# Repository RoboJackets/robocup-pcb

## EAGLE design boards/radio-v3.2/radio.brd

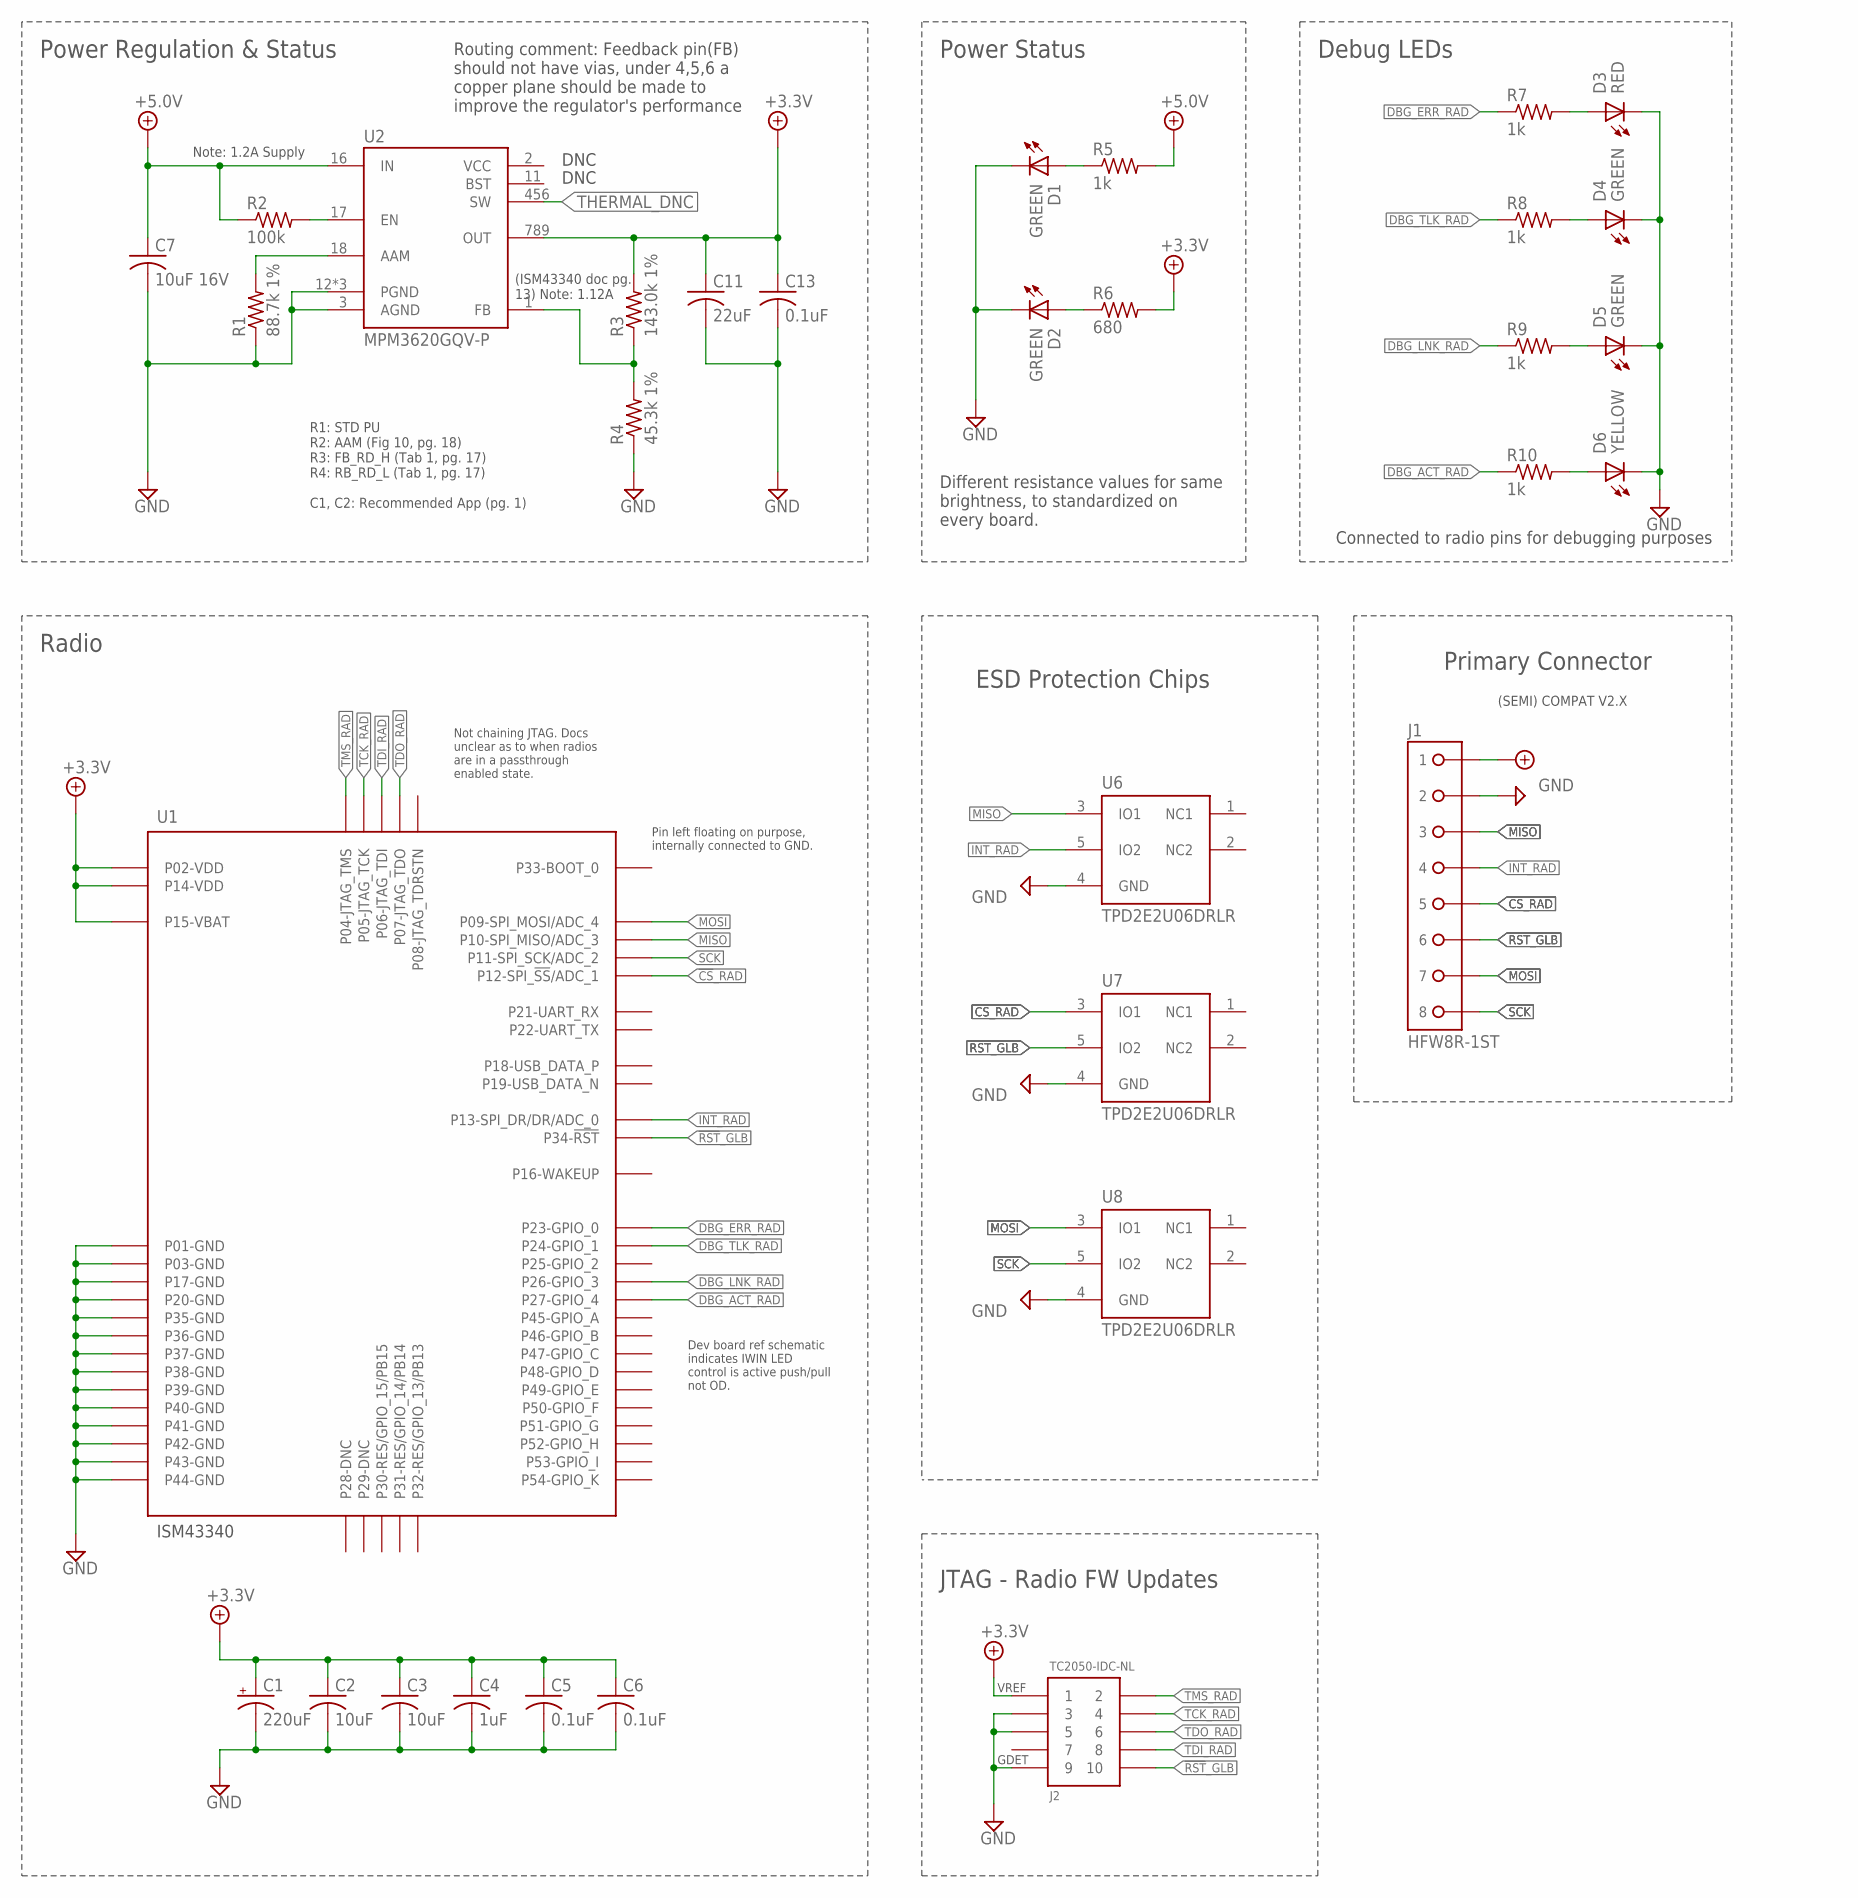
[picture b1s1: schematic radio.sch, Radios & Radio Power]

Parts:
C1: 220uF; ECA-0JM221-HGT_HORIZ
C2, C3: 10uF; C0805
C4: 1uF; C0603
C5, C6, C13: 0.1uF; C0603
C7: 10uF 16V; C1210
C11: 22uF; C1210
D1, D2, D4, D5: GREEN; CHIP-LED0603
D3: RED; CHIP-LED0603
D6: YELLOW; CHIP-LED0603
J1: HFW8R-1ST
J2: TC2050-IDC-NL
R1: 88.7k 1%; R0603
R2: 100k; R0603
R3: 143.0k 1%; R0603
R4: 45.3k 1%; R0603
R5, R7, R8, R9, R10: 1k; R0603
R6: 680; R0603
U1: ISM43340
U2: MPM3620GQV-P
U6, U7, U8: TPD2E2U06DRLR; SOT-553

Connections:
3V3_PWR_IND: D2.A, R6.1
5V_PWR_IND: D1.A, R5.1
!CS!_RAD: J1.5, U1.P$12 (P12-SPI_!SS!/ADC_1), U7.3 (IO1)
!RST!_GLB: J1.6, J2.10, U1.P$34 (P34-!RST!), U7.5 (IO2)
+3.3V: C1.P$1 (+), C2.1, C3.1, C4.1, C5.1, C6.1, C11.1, C13.1, J2.1, R3.2, R6.2, U1.P$2 (P02-VDD), U1.P$14 (P14-VDD), U1.P$15 (P15-VBAT), U2.789 (OUT)
+5.0V: C7.1, J1.1, R2.1, R5.2, U2.16 (IN)
AAM: R1.2, U2.18 (AAM)
DBG_ACT_RAD: R10.1, U1.P$27 (P27-GPIO_4)
DBG_ERR: D3.A, R7.2
DBG_ERR_RAD: R7.1, U1.P$23 (P23-GPIO_0)
DBG_LNK_RAD: R9.1, U1.P$26 (P26-GPIO_3)
DBG_TLK_RAD: R8.1, U1.P$24 (P24-GPIO_1)
DGB_ACT: D6.A, R10.2
DGB_LNK: D5.A, R9.2
EN: R2.2, U2.17 (EN)
FB: R3.1, R4.2, U2.1 (FB)
GND: C1.P$2 (-), C2.2, C3.2, C4.2, C5.2, C6.2, C7.2, C11.2, C13.2, D1.C (K), D2.C (K), D3.C (K), D4.C (K), D5.C (K), D6.C (K), J1.2, J2.3, J2.5, J2.9, R1.1, R4.1, U1.P$1 (P01-GND), U1.P$3 (P03-GND), U1.P$17 (P17-GND), U1.P$20 (P20-GND), U1.P$35 (P35-GND), U1.P$36 (P36-GND), U1.P$37 (P37-GND), U1.P$38 (P38-GND), U1.P$39 (P39-GND), U1.P$40 (P40-GND), U1.P$41 (P41-GND), U1.P$42 (P42-GND), U1.P$43 (P43-GND), U1.P$44 (P44-GND), U2.3 (AGND), U2.12 (PGND), U2.13 (PGND), U2.14 (PGND), U6.4 (GND), U7.4 (GND), U8.4 (GND)
INT_RAD: J1.4, U1.P$13 (P13-SPI_DR/DR/ADC_0), U6.5 (IO2)
MISO: J1.3, U1.P$10 (P10-SPI_MISO/ADC_3), U6.3 (IO1)
MOSI: J1.7, U1.P$9 (P09-SPI_MOSI/ADC_4), U8.3 (IO1)
SCK: J1.8, U1.P$11 (P11-SPI_SCK/ADC_2), U8.5 (IO2)
TCK_RAD: J2.4, U1.P$5 (P05-JTAG_TCK)
TDI_RAD: J2.8, U1.P$6 (P06-JTAG_TDI)
TDO_RAD: J2.6, U1.P$7 (P07-JTAG_TDO)
THERMAL_DNC: U2.456 (SW)
TLK: D4.A, R8.2
TMS_RAD: J2.2, U1.P$4 (P04-JTAG_TMS)

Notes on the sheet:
DNC
Primary Connector
Power Regulation & Status
Power Status
Note: 1.2A Supply
(ISM43340 doc pg. 13) Note: 1.12A
R1: STD PU R2: AAM (Fig 10, pg. 18) R3: FB_RD_H (Tab 1, pg. 17) R4: RB_RD_L (Tab 1, pg. 17) C1, C2: Recommended App (pg. 1)
Radio
Debug LEDs
VREF
GDET
JTAG - Radio FW Updates
Dev board ref schematic indicates IWIN LED control is active push/pull not OD.
Not chaining JTAG. Docs unclear as to when radios are in a passthrough enabled state.
(SEMI) COMPAT V2.X
ESD Protection Chips
Pin left floating on purpose, internally connected to GND.
Routing comment: Feedback pin(FB) should not have vias, under 4,5,6 a copper plane should be made to improve the regulator's performance
Connected to radio pins for debugging purposes
Different resistance values for same brightness, to standardized on every board.

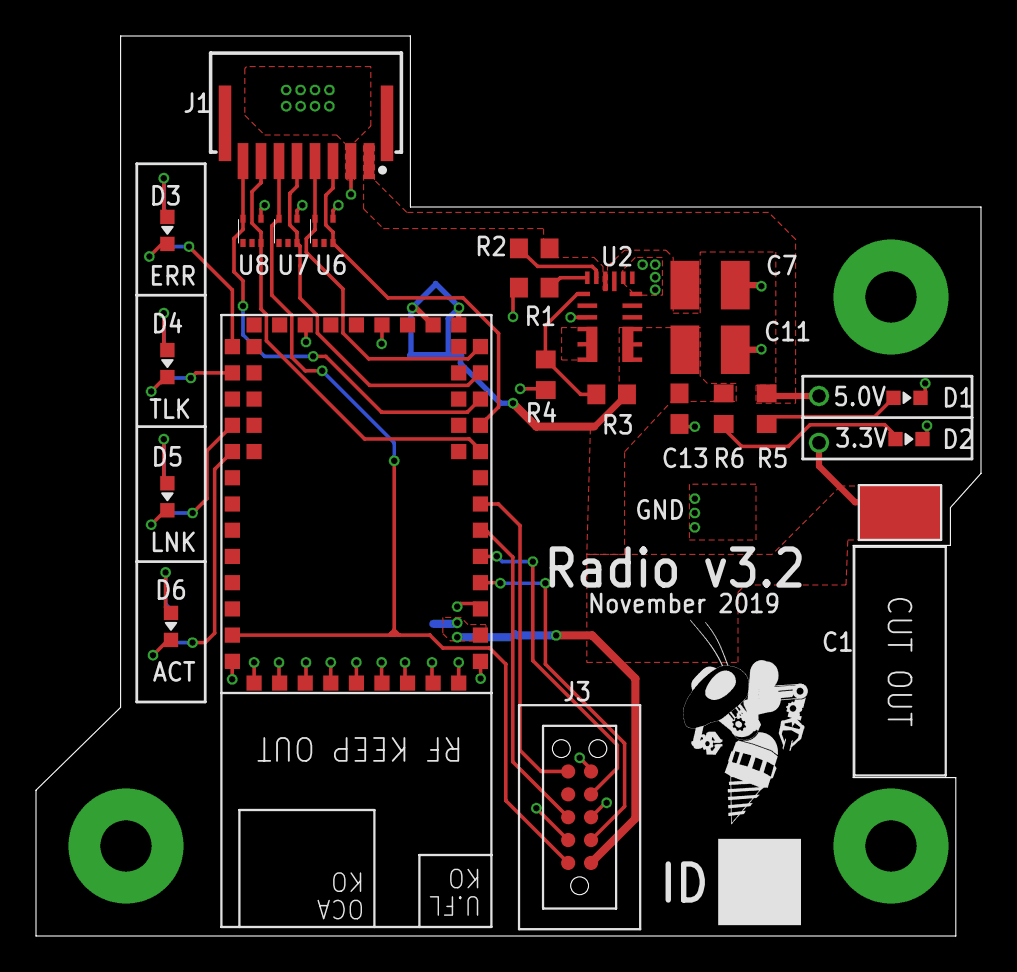
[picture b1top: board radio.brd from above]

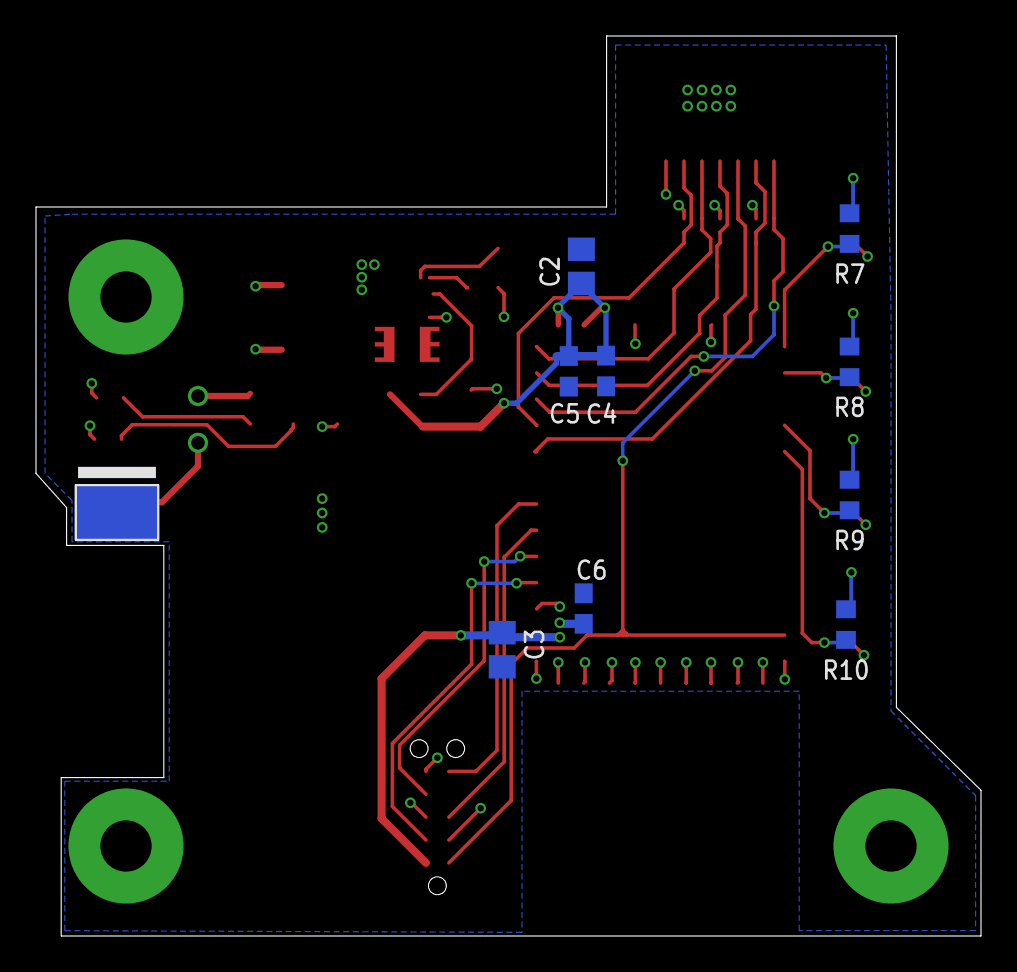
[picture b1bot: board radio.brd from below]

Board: 2 copper layers, 52.5 x 50.0 mm, 33 parts (9 on the bottom side), 26 nets.

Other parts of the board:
U$1: ROBOBUZZ_0.6X

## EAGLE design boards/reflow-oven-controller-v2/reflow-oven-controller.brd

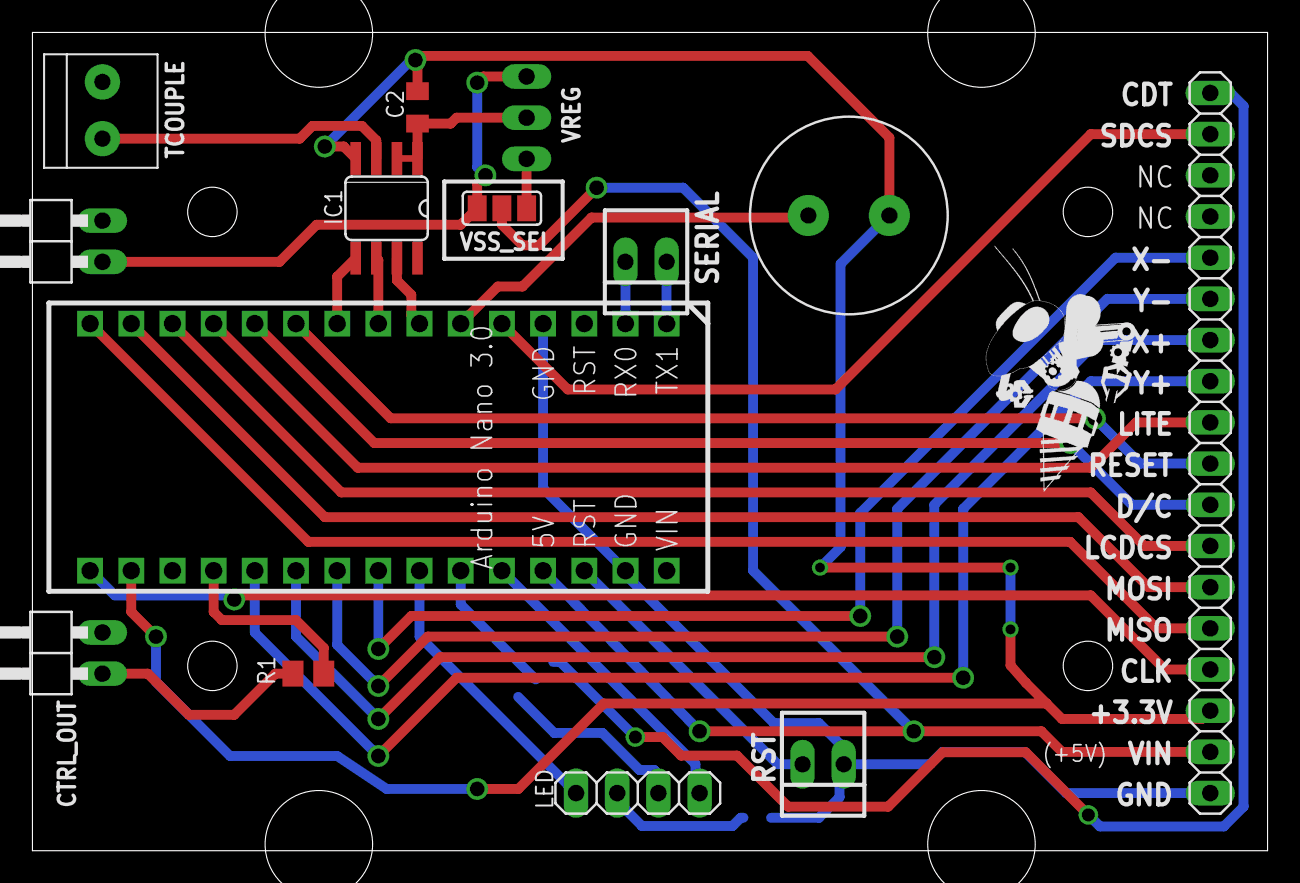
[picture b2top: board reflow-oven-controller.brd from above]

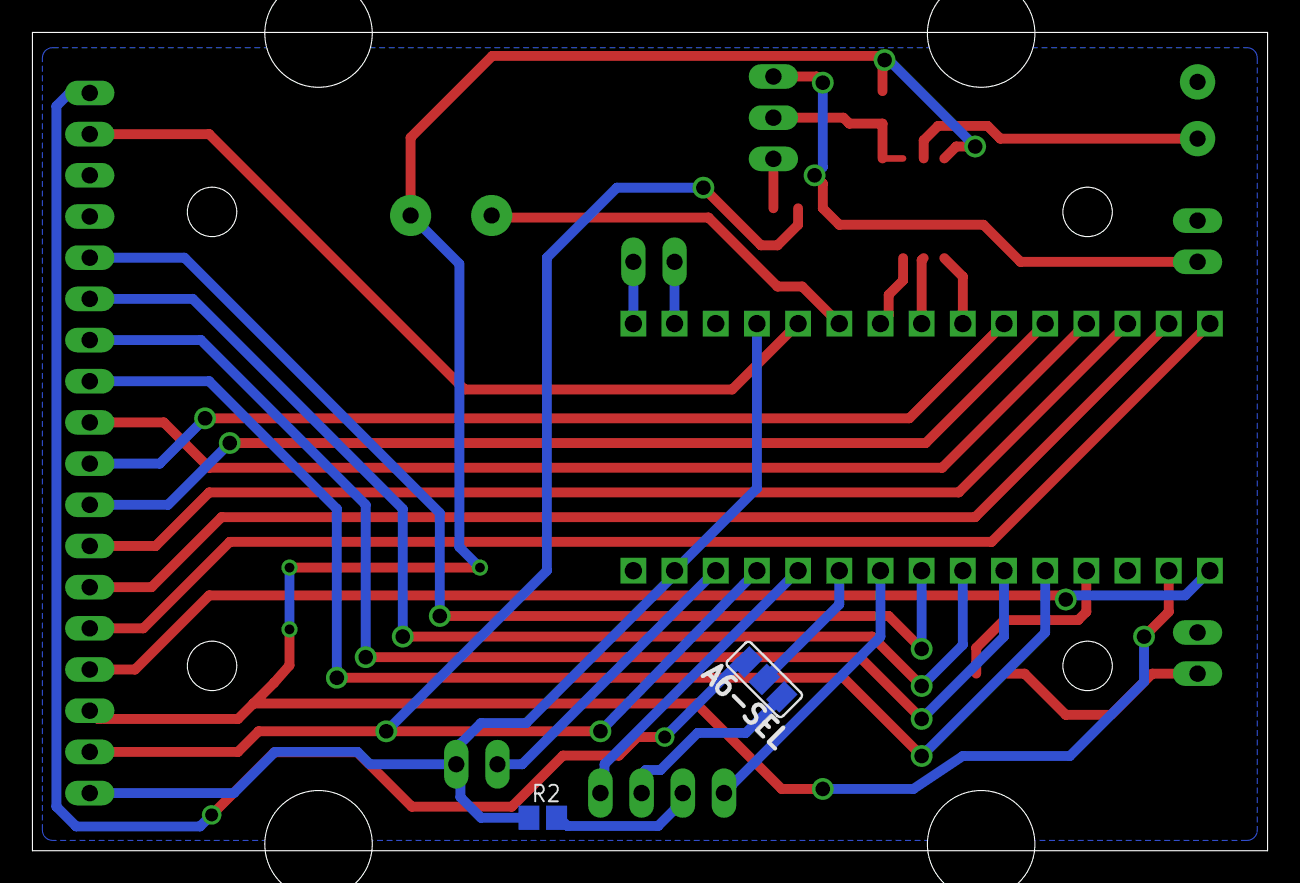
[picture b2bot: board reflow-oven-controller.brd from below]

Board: 2 copper layers, 76.2 x 50.5 mm, 17 parts (2 on the bottom side), 33 nets.

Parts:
A6-SEL: SJ_2
C2: 0.1uF; C0805K
IC1: MAX6675; SO08
JP1: CTRL_OUT; 1X02/90
JP2: VIN; 1X02/90
JP4: 1X18
LED: RGB Led Common Anode; 1X04
R1: 60; M0805
R2: R0805
RST: 22-23-2021
SERIAL: 22-23-2021
SP1: Speaker; PS12
TCOUPLE: 1X2-3.5MM; 3.5MMTERM
U$1: ANANO3.3; ANANO3.0
U$2: ROBOBUZZ_0.8X
VREG: 78SR
VSS_SEL: SJ_2

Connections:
A0: R1.1, U$1.A0
A5: LED.4, U$1.A5
A6: A6-SEL.2, U$1.A6
A7: LED.1, U$1.A7
BACKLIGHT: JP4.10, U$1.D9
CARDDET: A6-SEL.3, JP4.18
D/C: JP4.8, U$1.D8
DO: IC1.7, U$1.D4
GND: C2.2, IC1.1, IC1.2, JP1.2, JP2.2, JP4.1, R2.1, RST.1, TCOUPLE.2, U$1.GND, U$1.GND2, VREG.GND
LCDCS: JP4.7, U$1.D10
MISO: JP4.5, U$1.D12
MOSI: JP4.6, U$1.D11
unnamed: IC1.3, TCOUPLE.1
unnamed: A6-SEL.1, LED.2
unnamed: JP1.1, R1.2
unnamed: LED.3, R2.2
REGOUT: VREG.OUT, VSS_SEL.1
RESET: JP4.9, U$1.D7
RST2: RST.2, U$1.RST2
RX0: SERIAL.2, U$1.RX0
SCLK: JP4.4, U$1.D13
SDCS: JP4.17, U$1.D2
SPK: SP1.P$1, U$1.D3
TCS: IC1.6, U$1.D5
TRANSIN: JP2.1, VREG.IN, VSS_SEL.3
TSCK: IC1.5, U$1.D6
TX1: SERIAL.1, U$1.TX1
VCC: JP4.2, U$1.5V, VSS_SEL.2
VSS: C2.1, IC1.4, JP4.3, SP1.P$2, U$1.3V3
X+: JP4.12, U$1.A2
X-: JP4.14, U$1.A4
Y+: JP4.11, U$1.A1
Y-: JP4.13, U$1.A3

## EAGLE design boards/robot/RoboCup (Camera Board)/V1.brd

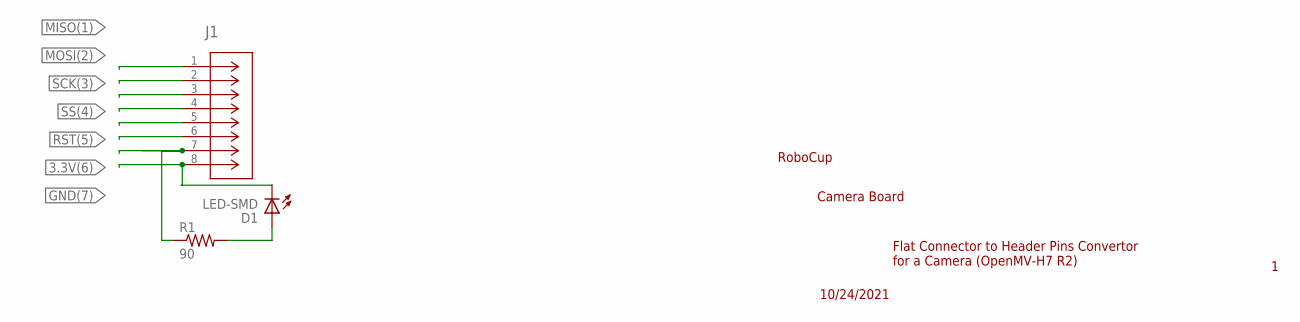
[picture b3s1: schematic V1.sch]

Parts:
D1: LED-SMD; CHIP-LED0603
J1: 5034800800; CONN_503480-0800_MOL
R1: 90; R0603W

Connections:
3.3V(6): J1.6
-: D1.C (K), J1.8
GND(7): J1.7, R1.1 (PIN1)
MISO(1): J1.1
MOSI(2): J1.2
unnamed: D1.A, R1.2 (PIN2)
RST(5): J1.5
SCK(3): J1.3
SS(4): J1.4

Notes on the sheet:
Camera Board
RoboCup
Flat Connector to Header Pins Convertor for a Camera (OpenMV-H7 R2)
10/24/2021

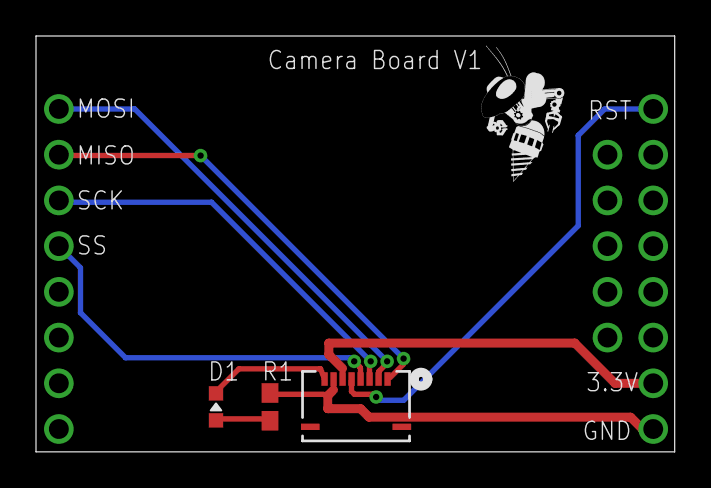
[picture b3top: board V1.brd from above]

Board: 2 copper layers, 35.5 x 23.1 mm, 4 parts (0 on the bottom side), 3 nets.

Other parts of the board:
E$1: ROBOBUZZ_0.4X

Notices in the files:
parts and their libraries:
Jlink-Connector: COPYRIGHT: Copyright (C) 2022 Ultra Librarian. All rights reserved.
COPYRIGHT: Copyright (C) 2021 Ultra Librarian. All rights reserved.
